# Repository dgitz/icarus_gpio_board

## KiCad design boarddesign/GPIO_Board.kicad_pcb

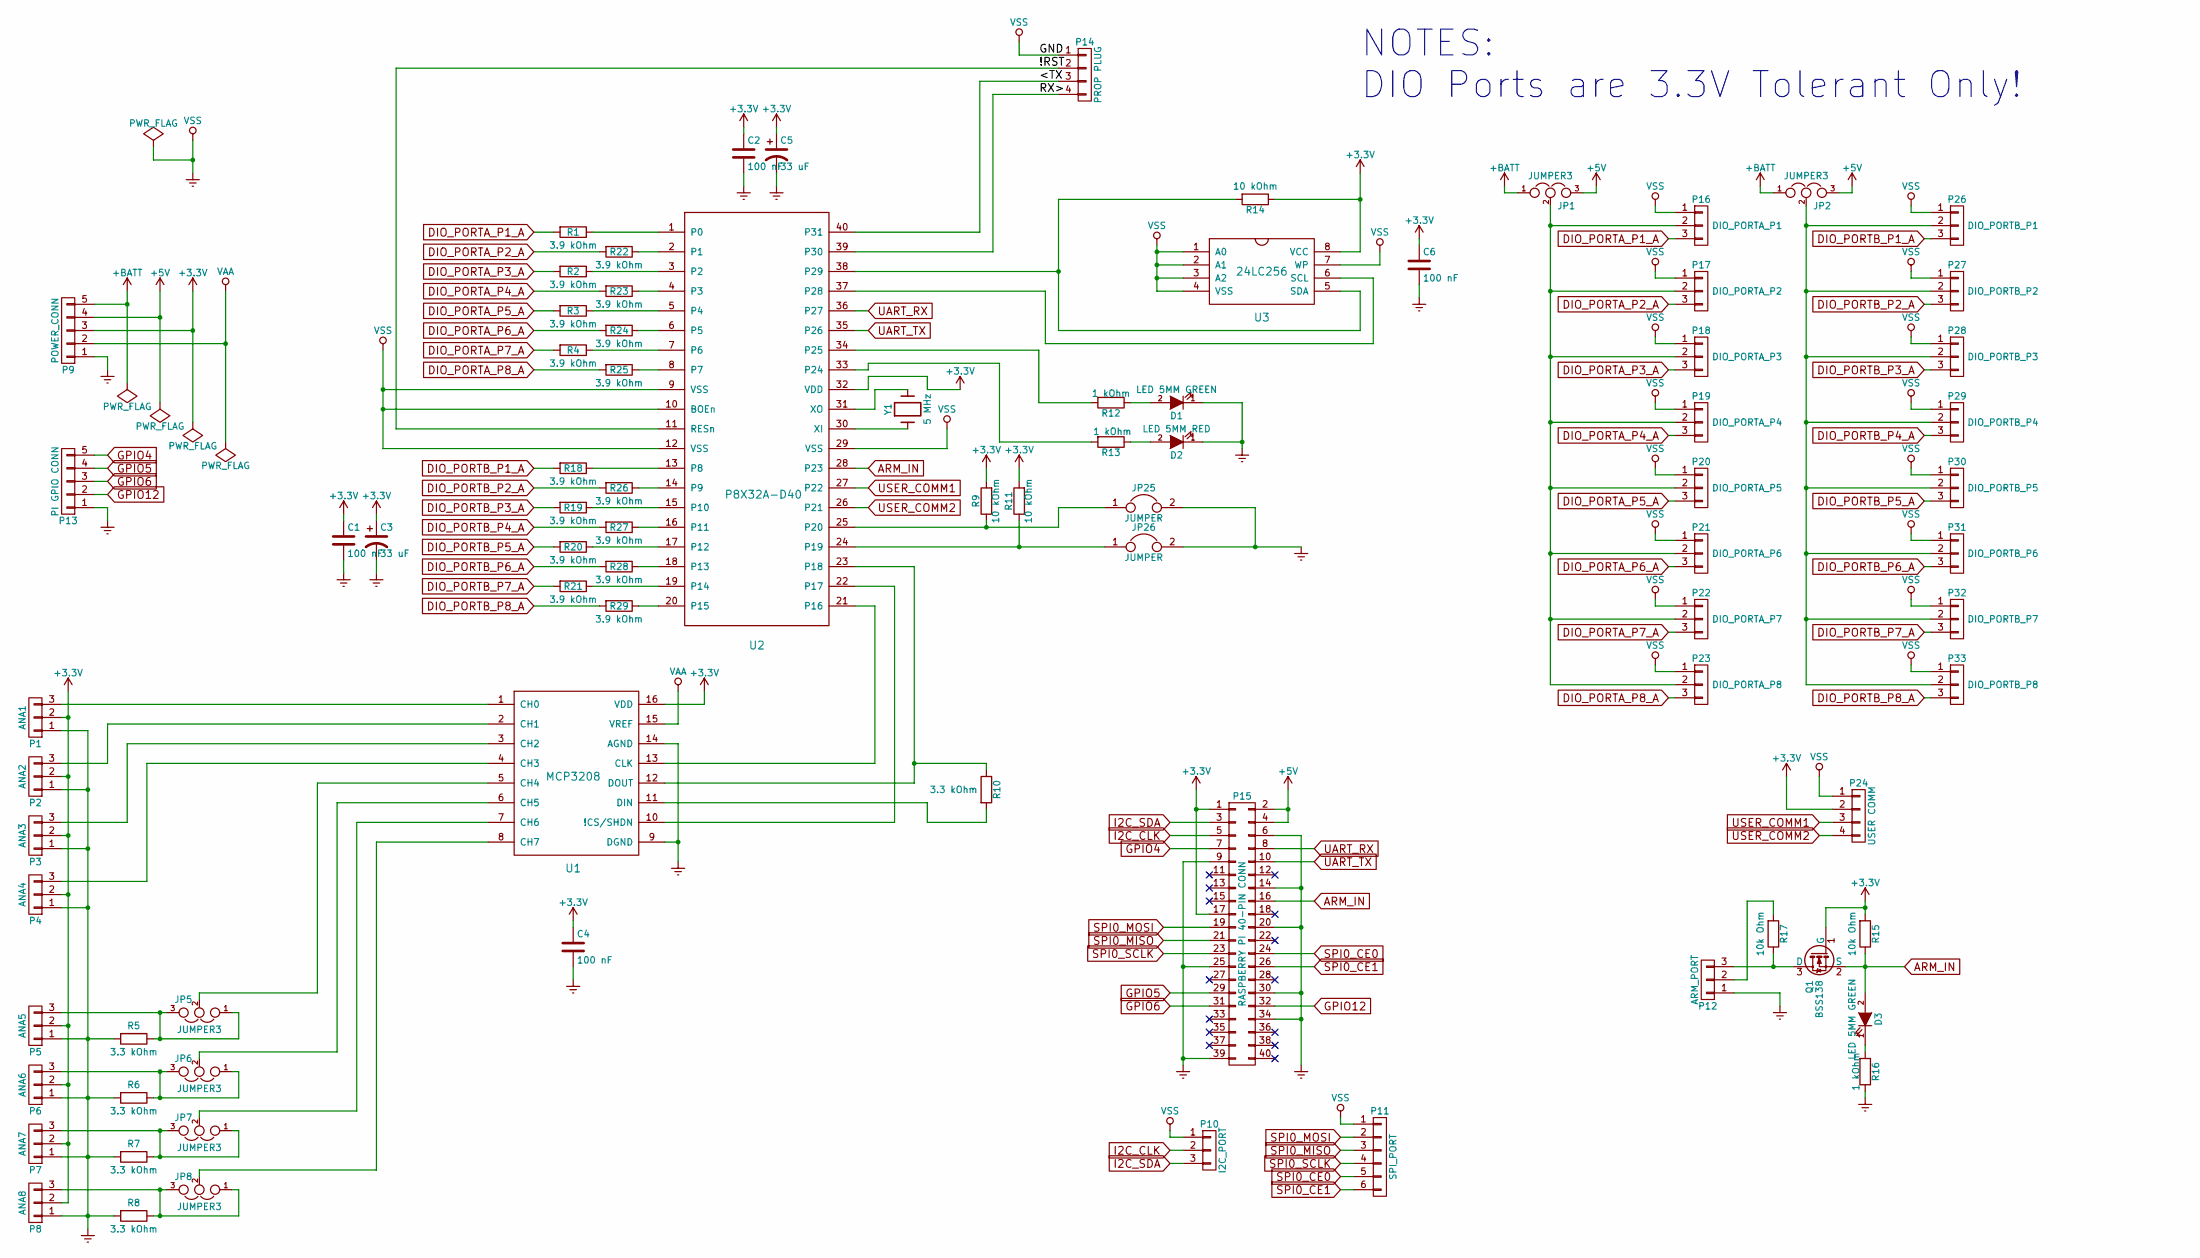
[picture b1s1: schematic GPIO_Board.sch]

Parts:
C1, C2, C4, C6: 100 nF; C_Rect_L7_W2.5_P5
C3, C5: 33 uF; C_Radial_D5_L6_P2.5
D1, D3: LED 5MM GREEN; LED-5MM
D2: LED 5MM RED; LED-5MM
JP1, JP2, JP5, JP6, JP7, JP8: JUMPER3; Pin_Header_Straight_1x03
JP25, JP26: JUMPER; Pin_Header_Straight_1x02
P1: ANA1; Pin_Header_Straight_1x03
P2: ANA2; Pin_Header_Straight_1x03
P3: ANA3; Pin_Header_Straight_1x03
P4: ANA4; Pin_Header_Straight_1x03
P5: ANA5; Pin_Header_Straight_1x03
P6: ANA6; Pin_Header_Straight_1x03
P7: ANA7; Pin_Header_Straight_1x03
P8: ANA8; Pin_Header_Straight_1x03
P9: POWER_CONN; TerminalBlock_Pheonix_MPT-2.54mm_5pol
P10: I2C_PORT; Pin_Header_Straight_1x03
P11: SPI_PORT; Pin_Header_Straight_1x06
P12: ARM_PORT; TerminalBlock_Pheonix_MPT-2.54mm_3pol
P13: PI GPIO CONN; TerminalBlock_Pheonix_MPT-2.54mm_5pol
P14: PROP PLUG; Pin_Header_Angled_1x04
P15: RASPBERRY PI 40-PIN CONN; Pin_Header_Straight_2x20
P16: DIO_PORTA_P1; Pin_Header_Straight_1x03
P17: DIO_PORTA_P2; Pin_Header_Straight_1x03
P18: DIO_PORTA_P3; Pin_Header_Straight_1x03
P19: DIO_PORTA_P4; Pin_Header_Straight_1x03
P20: DIO_PORTA_P5; Pin_Header_Straight_1x03
P21: DIO_PORTA_P6; Pin_Header_Straight_1x03
P22: DIO_PORTA_P7; Pin_Header_Straight_1x03
P23: DIO_PORTA_P8; Pin_Header_Straight_1x03
P24: USER COMM; TerminalBlock_Pheonix_MPT-2.54mm_4pol
P26: DIO_PORTB_P1; Pin_Header_Straight_1x03
P27: DIO_PORTB_P2; Pin_Header_Straight_1x03
P28: DIO_PORTB_P3; Pin_Header_Straight_1x03
P29: DIO_PORTB_P4; Pin_Header_Straight_1x03
P30: DIO_PORTB_P5; Pin_Header_Straight_1x03
P31: DIO_PORTB_P6; Pin_Header_Straight_1x03
P32: DIO_PORTB_P7; Pin_Header_Straight_1x03
P33: DIO_PORTB_P8; Pin_Header_Straight_1x03
Q1: BSS138; SOT-23_Handsoldering
R1, R2, R3, R4, R18, R19, R20, R21, R22, R23, R24, R25, R26, R27, R28, R29: 3.9 kOhm; Pin_Header_Straight_1x02
R5, R6, R7, R8: 3.3 kOhm; Pin_Header_Straight_1x02
R9, R11, R14: 10 kOhm; Resistor_Horizontal_RM10mm
R10: 3.3 kOhm; Resistor_Horizontal_RM10mm
R12, R13, R16: 1 kOhm; Resistor_Horizontal_RM10mm
R15, R17: 10k Ohm; Resistor_Horizontal_RM10mm
U1: MCP3208; DIP-16_W7.62mm
U2: P8X32A-D40; DIP-40_W15.24mm
U3: 24LC256; DIP-8_W7.62mm
Y1: 5 MHz; Crystal_HC49-U_Vertical

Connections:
+3V3: C1.1, C2.1, C3.1, C4.1, C5.1, C6.1, P1.2, P2.2, P3.2, P4.2, P5.2, P6.2, P7.2, P8.2, P9.3, P15.1, P15.17, P24.2, Q1.1 (G), R9.2, R11.2, R14.1, R15.2, U1.16 (VDD), U2.32 (VDD), U3.8 (VCC)
+5V: JP1.3, JP2.3, P9.4, P15.2, P15.4
+BATT: JP1.1, JP2.1, P9.5
/!RST: P14.2, U2.11 (RESn)
/<TX: P14.3, U2.40 (P31)
/RX>: P14.4, U2.39 (P30)
ARM_IN: D3.2 (A), P15.16, Q1.2 (S), R15.1, U2.28 (P23)
DIO_PORTA_P1_A: P16.3, R1.2
DIO_PORTA_P2_A: P17.3, R22.2
DIO_PORTA_P3_A: P18.3, R2.2
DIO_PORTA_P4_A: P19.3, R23.2
DIO_PORTA_P5_A: P20.3, R3.2
DIO_PORTA_P6_A: P21.3, R24.2
DIO_PORTA_P7_A: P22.3, R4.2
DIO_PORTA_P8_A: P23.3, R25.2
DIO_PORTB_P1_A: P26.3, R18.2
DIO_PORTB_P2_A: P27.3, R26.2
DIO_PORTB_P3_A: P28.3, R19.2
DIO_PORTB_P4_A: P29.3, R27.2
DIO_PORTB_P5_A: P30.3, R20.2
DIO_PORTB_P6_A: P31.3, R28.2
DIO_PORTB_P7_A: P32.3, R21.2
DIO_PORTB_P8_A: P33.3, R29.2
GNDREF: C1.2, C2.2, C3.2, C4.2, C5.2, C6.2, D1.1 (K), D2.1 (K), JP25.2, JP26.2, P1.1, P2.1, P3.1, P4.1, P5.1, P6.1, P7.1, P8.1, P9.1, P10.1, P11.1, P12.1, P13.1, P14.1, P15.6, P15.9, P15.14, P15.20, P15.25, P15.30, P15.34, P15.39, P16.1, P17.1, P18.1, P19.1, P20.1, P21.1, P22.1, P23.1, P24.1, P26.1, P27.1, P28.1, P29.1, P30.1, P31.1, P32.1, P33.1, R5.2, R6.2, R7.2, R8.2, R16.1, U1.9 (DGND), U1.14 (AGND), U2.9 (VSS), U2.10 (BOEn), U2.12 (VSS), U2.29 (VSS), U3.1 (A0), U3.2 (A1), U3.3 (A2), U3.4 (VSS), U3.7 (WP)
GPIO4: P13.5, P15.7
GPIO5: P13.4, P15.29
GPIO6: P13.3, P15.31
GPIO12: P13.2, P15.32
I2C_CLK: P10.2, P15.5
I2C_SDA: P10.3, P15.3
unnamed: D1.2 (A), R12.1
unnamed: D2.2 (A), R13.1
unnamed: D3.1 (K), R16.2
unnamed: JP1.2, P16.2, P17.2, P18.2, P19.2, P20.2, P21.2, P22.2, P23.2
unnamed: JP2.2, P26.2, P27.2, P28.2, P29.2, P30.2, P31.2, P32.2, P33.2
unnamed: JP5.1, JP5.3, P5.3, R5.1
unnamed: JP5.2, U1.5 (CH4)
unnamed: JP6.1, JP6.3, P6.3, R6.1
unnamed: JP6.2, U1.6 (CH5)
unnamed: JP7.1, JP7.3, P7.3, R7.1
unnamed: JP7.2, U1.7 (CH6)
unnamed: JP8.1, JP8.3, P8.3, R8.1
unnamed: JP8.2, U1.8 (CH7)
unnamed: JP25.1, R9.1, U2.25 (P20)
unnamed: JP26.1, R11.1, U2.24 (P19)
unnamed: P1.3, U1.1 (CH0)
unnamed: P2.3, U1.2 (CH1)
unnamed: P3.3, U1.3 (CH2)
unnamed: P4.3, U1.4 (CH3)
unnamed: P12.2, R17.2
unnamed: P12.3, Q1.3 (D), R17.1
unnamed: R1.1, U2.1 (P0)
unnamed: R2.1, U2.3 (P2)
unnamed: R3.1, U2.5 (P4)
unnamed: R4.1, U2.7 (P6)
unnamed: R10.1, U1.12 (DOUT), U2.23 (P18)
unnamed: R10.2, U1.11 (DIN)
unnamed: R12.2, U2.34 (P25)
unnamed: R13.2, U2.33 (P24)
unnamed: R14.2, U2.38 (P29), U3.5 (SDA)
unnamed: R18.1, U2.13 (P8)
unnamed: R19.1, U2.15 (P10)
unnamed: R20.1, U2.17 (P12)
unnamed: R21.1, U2.19 (P14)
unnamed: R22.1, U2.2 (P1)
unnamed: R23.1, U2.4 (P3)
unnamed: R24.1, U2.6 (P5)
unnamed: R25.1, U2.8 (P7)
unnamed: R26.1, U2.14 (P9)
unnamed: R27.1, U2.16 (P11)
unnamed: R28.1, U2.18 (P13)
unnamed: R29.1, U2.20 (P15)
unnamed: U1.10 (!CS/SHDN), U2.22 (P17)
unnamed: U1.13 (CLK), U2.21 (P16)
unnamed: U2.30 (XI), Y1.1
unnamed: U2.31 (XO), Y1.2
unnamed: U2.37 (P28), U3.6 (SCL)
SPI0_CE0: P11.5, P15.24
SPI0_CE1: P11.6, P15.26
SPI0_MISO: P11.3, P15.21
SPI0_MOSI: P11.2, P15.19
SPI0_SCLK: P11.4, P15.23
UART_RX: P15.8, U2.36 (P27)
UART_TX: P15.10, U2.35 (P26)
USER_COMM1: P24.3, U2.27 (P22)
USER_COMM2: P24.4, U2.26 (P21)
VAA: P9.2, U1.15 (VREF)

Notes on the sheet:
NOTES: DIO Ports are 3.3V Tolerant Only!

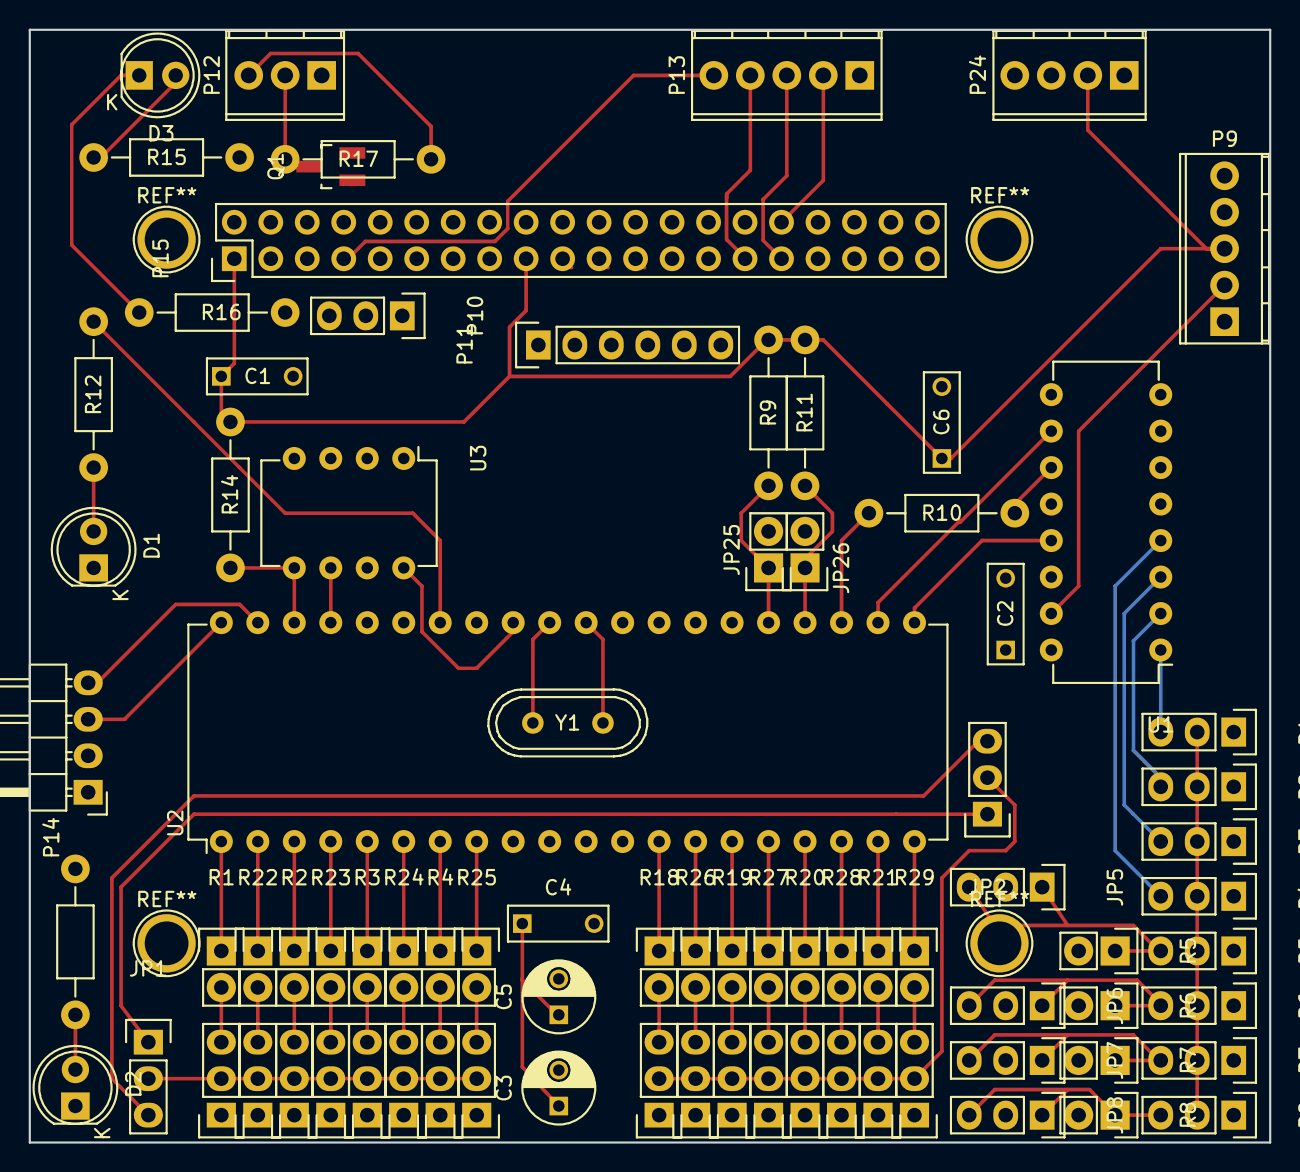
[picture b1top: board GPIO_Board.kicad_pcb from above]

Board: 2 copper layers, 86.4 x 77.5 mm, 83 parts (0 on the bottom side), 87 nets.

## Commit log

2016-08-12 Uart transceiver.
2016-08-13 Some work on implementing auto-generated serial message code.
2016-08-14 Major work done with encoding/decoding serial data based off auto-generated code.
2016-08-16 Some work on Diagnostics.
2016-08-16 Lots of work done in configuring and setting PortA
2016-08-18 Added in ADC serial message. Added in servo stuff.
2016-08-20 More work on getting DIO to work.
2016-09-08 Various changes and improvements.
2016-09-30 Fixed stability issue and checksum issue.
2016-10-01 PWM OUtput very responsive.
2016-11-09 Added ControlGroup code.
2016-11-19 Added current board design.
2016-11-23 Started routing board.
2016-11-27 More work on Arm/Disarm stuff.
